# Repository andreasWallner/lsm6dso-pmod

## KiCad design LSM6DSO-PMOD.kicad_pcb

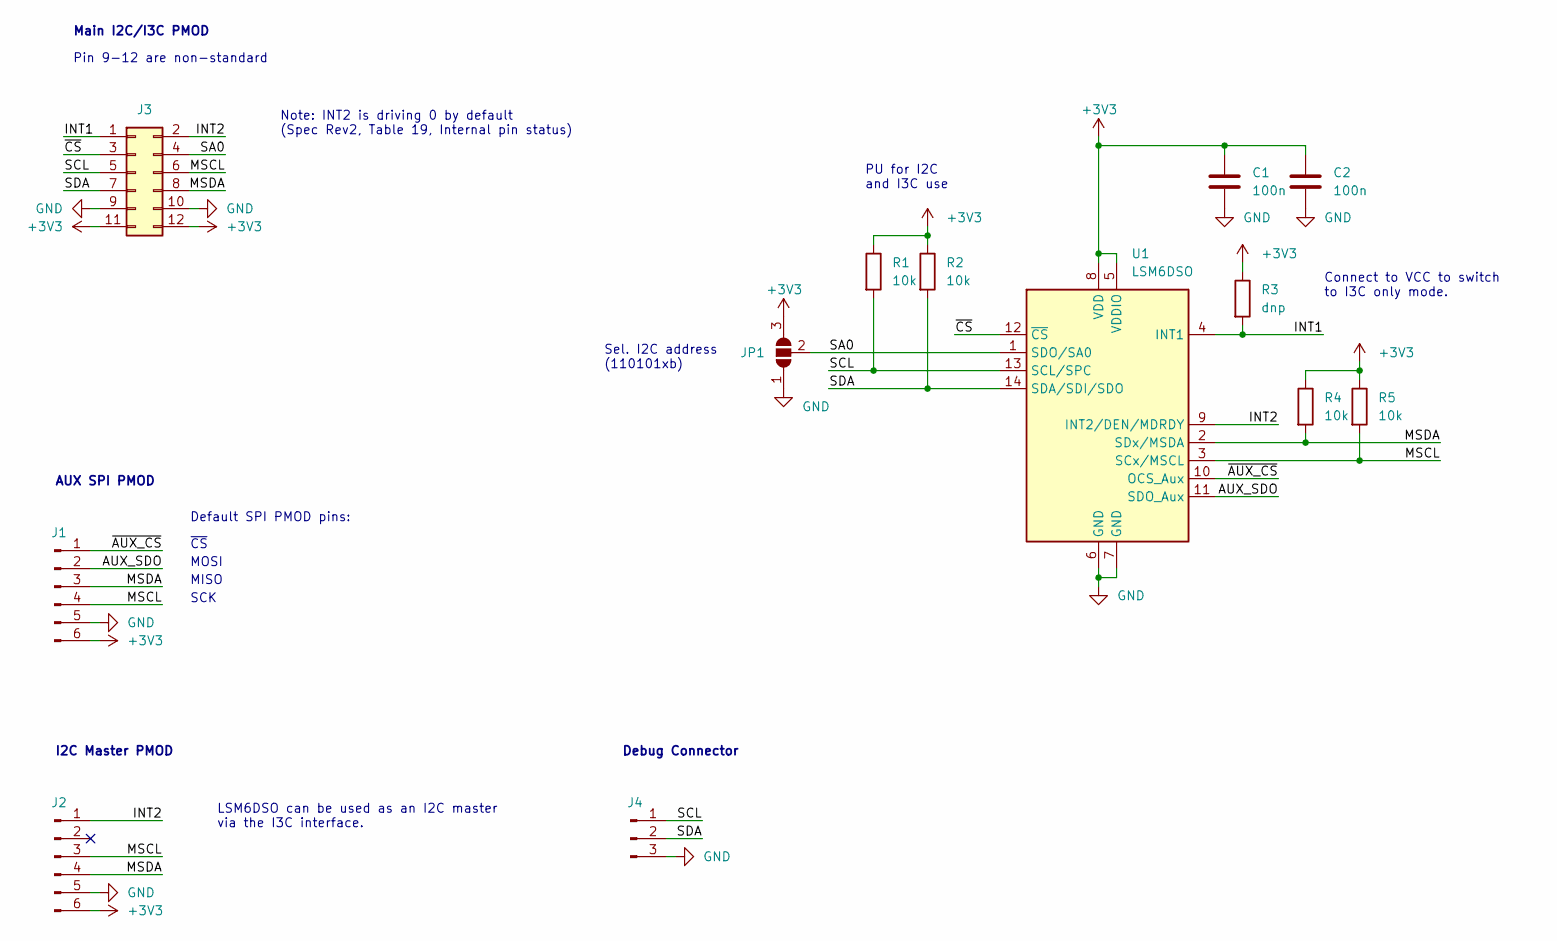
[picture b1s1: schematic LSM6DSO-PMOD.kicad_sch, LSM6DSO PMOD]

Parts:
C1, C2: 100n; C_0402_1005Metric
J1, J2: Conn_01x06_Male; PinHeader_1x06_P2.54mm_Vertical
J3: Conn_02x06_Counter_Clockwise; PinHeader_2x06_P2.54mm_Horizontal
J4: Conn_01x03_Male; PinHeader_1x03_P2.54mm_Vertical
JP1: SolderJumper_3_Open; SolderJumper-3_P2.0mm_Open_TrianglePad1.0x1.5mm
R1, R2, R4, R5: 10k; R_0603_1608Metric
R3: dnp; R_0603_1608Metric
U1: LSM6DSO; LGA-14_3x2.5mm_P0.5mm_LayoutBorder3x4y

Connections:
+3V3: C1.1, C2.1, J1.6, J2.6, J3.11, J3.12, JP1.3 (B), R1.1, R2.1, R3.1, R4.1, R5.1, U1.5 (VDDIO), U1.8 (VDD)
/AUX_SDO: J1.2, U1.11 (SDO_Aux)
/INT1: J3.1, R3.2, U1.4 (INT1)
/INT2: J2.1, J3.2, U1.9 (INT2/DEN/MDRDY)
/MSCL: J1.4, J2.3, J3.6, R5.2, U1.3 (SCx/MSCL)
/MSDA: J1.3, J2.4, J3.8, R4.2, U1.2 (SDx/MSDA)
/SA0: J3.4, JP1.2 (C), U1.1 (SDO/SA0)
/SCL: J3.5, J4.1, R1.2, U1.13 (SCL/SPC)
/SDA: J3.7, J4.2, R2.2, U1.14 (SDA/SDI/SDO)
/~AUX_CS: J1.1, U1.10 (OCS_Aux)
/~CS: J3.3, U1.12 (~CS)
GND: C1.2, C2.2, J1.5, J2.5, J3.9, J3.10, J4.3, JP1.1 (A), U1.6 (GND), U1.7 (GND)

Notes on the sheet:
LSM6DSO can be used as an I2C master via the I3C interface.
Debug Connector
I2C Master PMOD
MOSI
MISO
Note: INT2 is driving 0 by default (Spec Rev2, Table 19, Internal pin status)
Pin 9-12 are non-standard
Main I2C/I3C PMOD
Default SPI PMOD pins:
Connect to VCC to switch to I3C only mode.
PU for I2C and I3C use
AUX SPI PMOD
Sel. I2C address (110101xb)
SCK
~{CS}

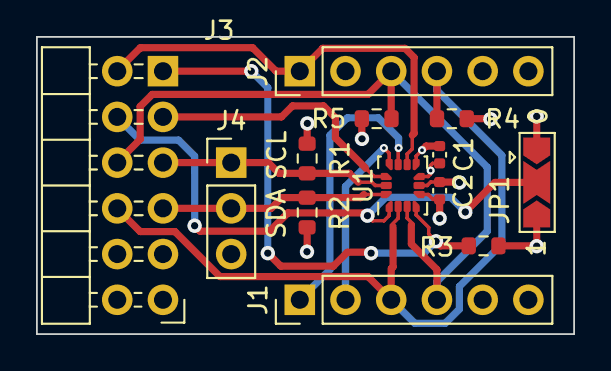
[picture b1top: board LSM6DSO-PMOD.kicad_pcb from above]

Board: 4 copper layers, 29.8 x 16.5 mm, 13 parts (0 on the bottom side), 12 nets.

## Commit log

2023-04-07 Initial version
